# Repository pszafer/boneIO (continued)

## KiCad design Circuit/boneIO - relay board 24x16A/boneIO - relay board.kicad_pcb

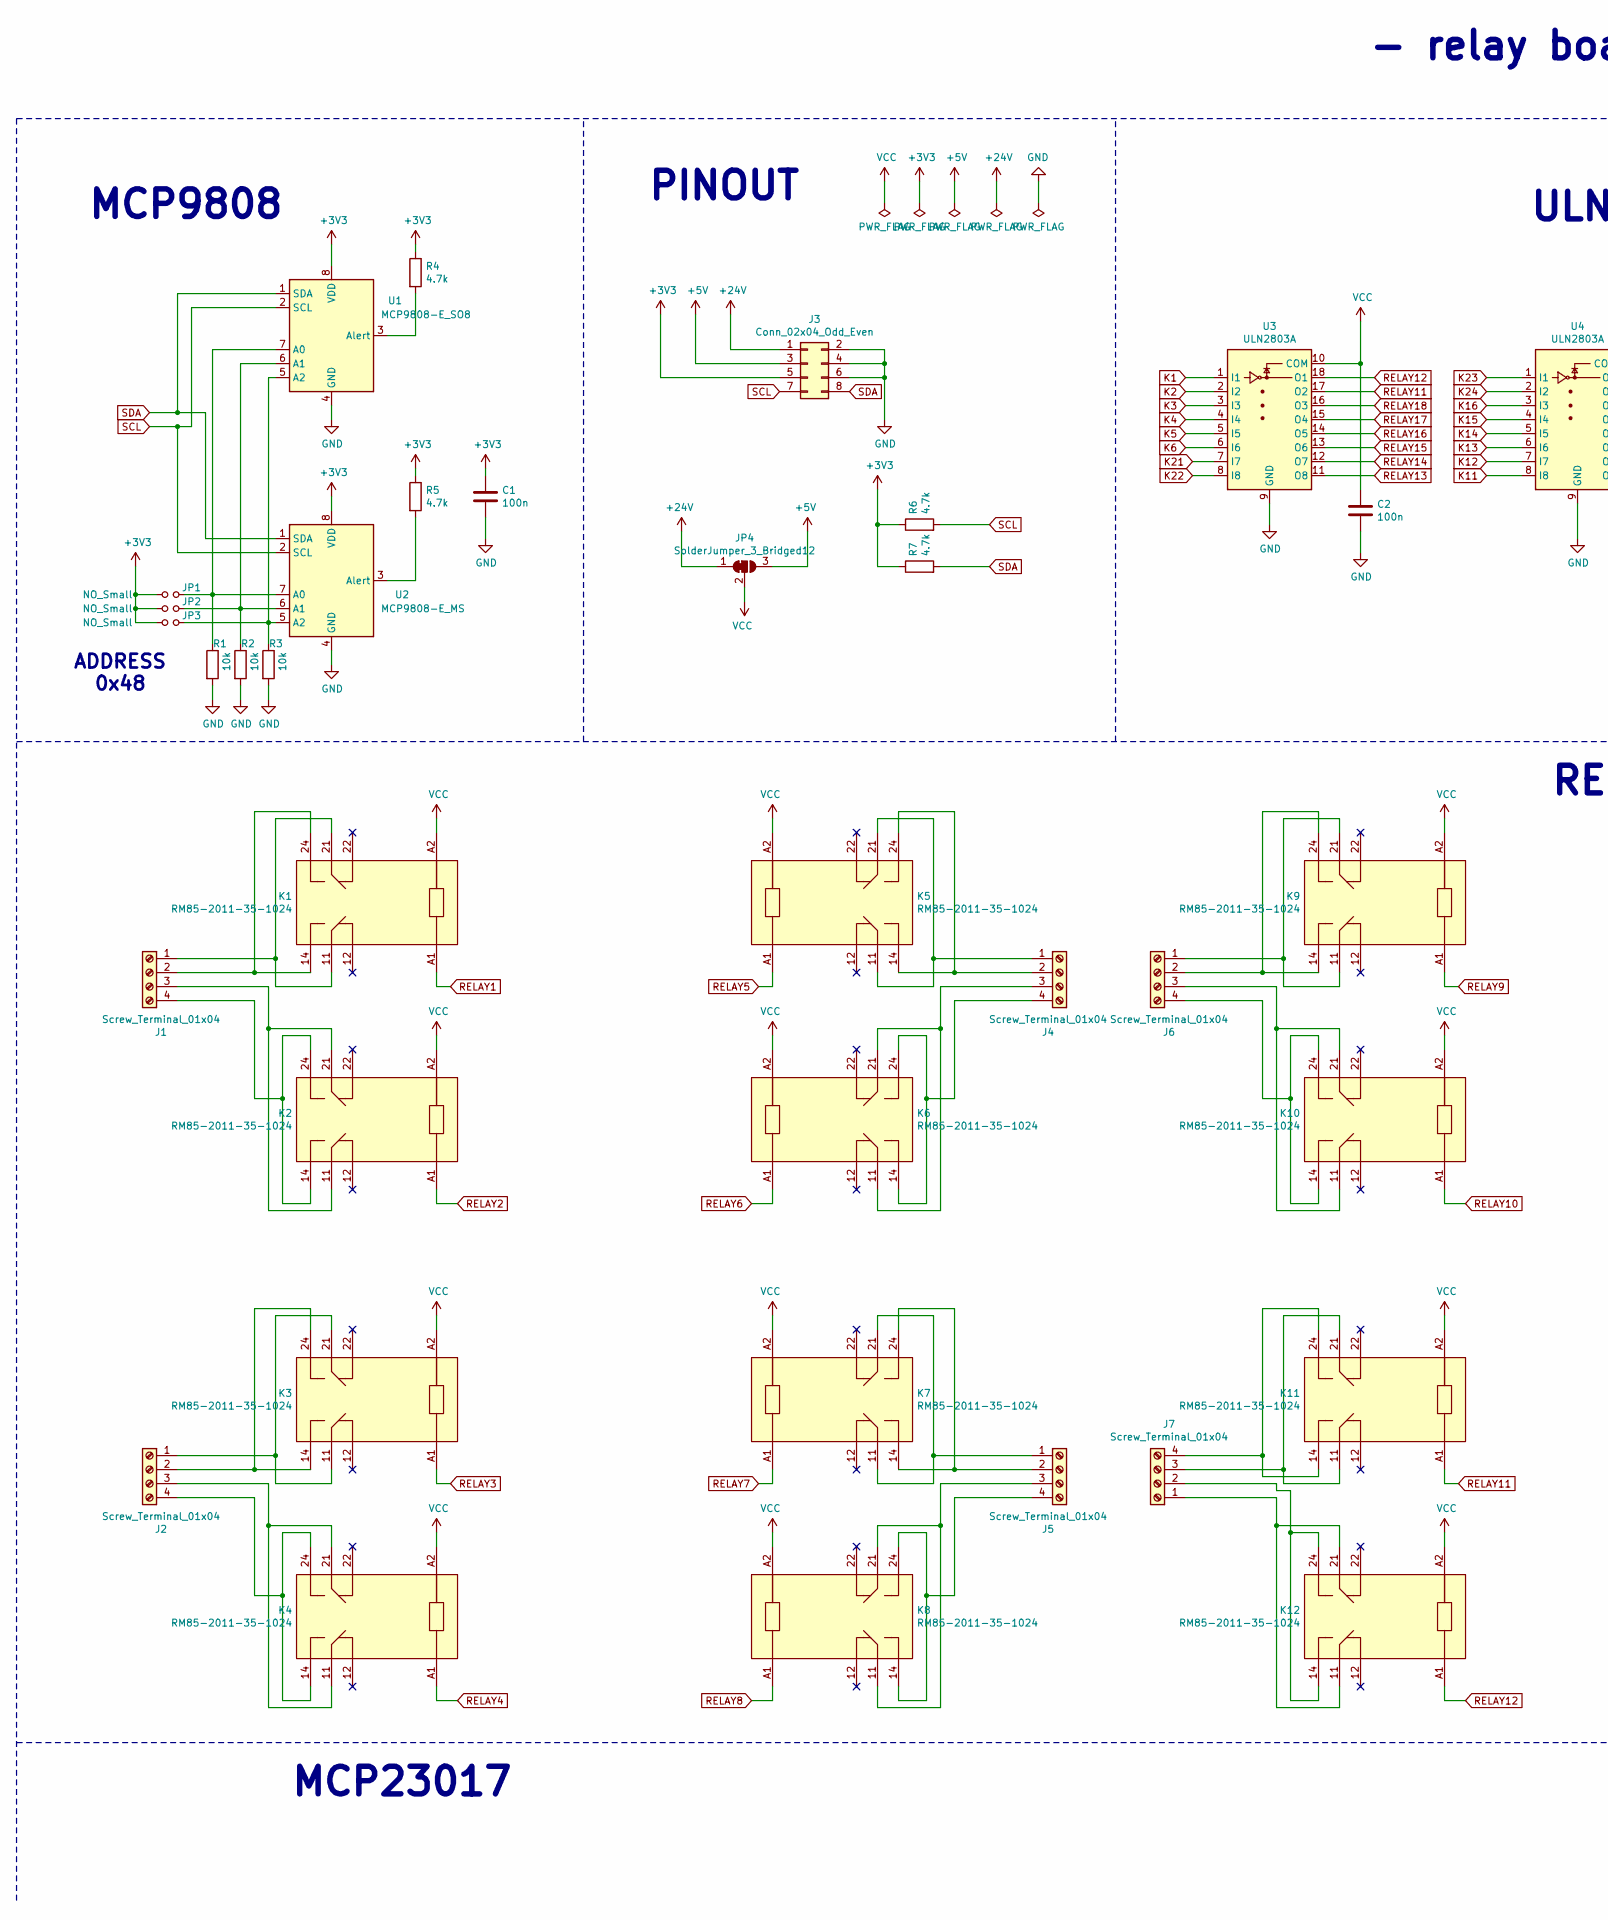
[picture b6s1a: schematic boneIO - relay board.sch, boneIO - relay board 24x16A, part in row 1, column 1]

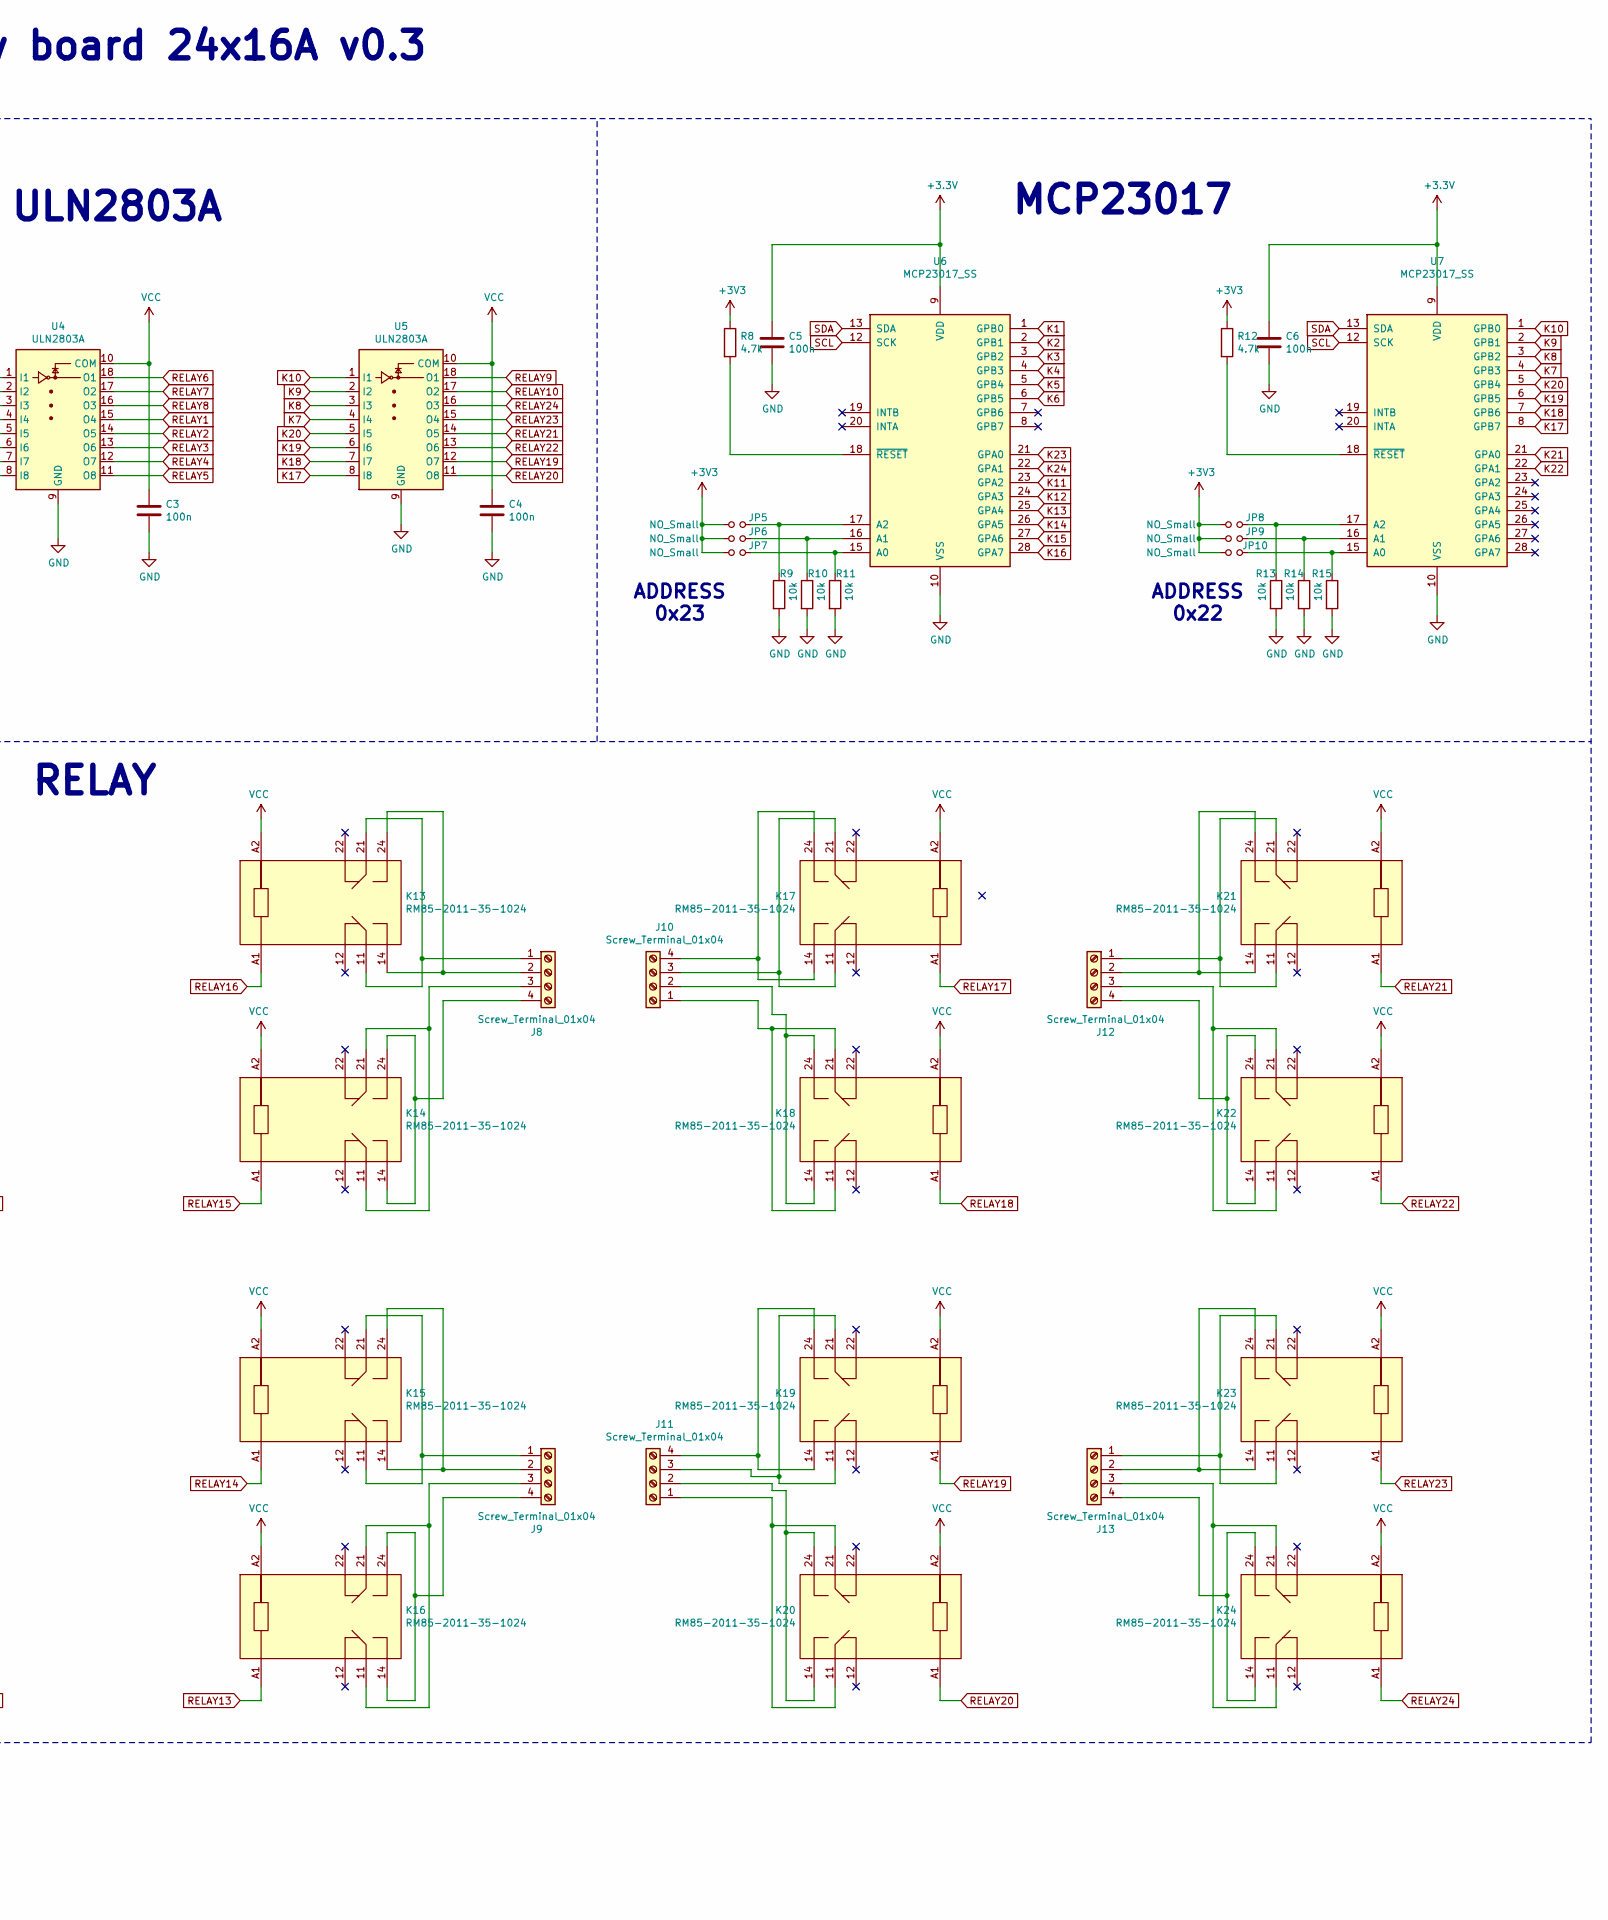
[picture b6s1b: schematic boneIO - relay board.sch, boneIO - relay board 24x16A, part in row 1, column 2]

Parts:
C1, C2, C3, C4, C5, C6: 100n; C_0603_1608Metric
J1, J2, J4, J5, J6, J7, J8, J9, J10, J11, J12, J13: Screw_Terminal_01x04; PhoenixContact_GMSTBA_2,5_4-G_1x04_P7.50mm_Horizontal
J3: Conn_02x04_Odd_Even; PinHeader_2x04_P2.54mm_Vertical
JP1, JP2, JP3, JP5, JP6, JP7, JP8, JP9, JP10: NO_Small; SolderJumper-2_P1.3mm_Open_RoundedPad1.0x1.5mm
JP4: SolderJumper_3_Bridged12; SolderJumper-3_P1.3mm_Bridged12_RoundedPad1.0x1.5mm
K1, K2, K3, K4, K5, K6, K7, K8, K9, K10, K11, K12, K13, K14, K15, K16, K17, K18, K19, K20, K21, K22, K23, K24: RM85-2011-35-1024; RM852011351024
R1, R2, R3, R9, R10, R11, R13, R14, R15: 10k; R_0603_1608Metric
R4, R5, R6, R7, R8, R12: 4.7k; R_0603_1608Metric
U1: MCP9808-E_SO8; SO-8_3.9x4.9mm_P1.27mm
U2: MCP9808-E_MS; SOP65P490X110-8N
U3, U4, U5: ULN2803A; SOIC-18W_7.5x11.6mm_P1.27mm
U6, U7: MCP23017_SS; SSOP-28_5.3x10.2mm_P0.65mm

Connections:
+5V: J3.3, JP4.3 (B)
+24V: J3.1, JP4.1 (A)
GND: C1.2, C2.2, C3.2, C4.2, C5.2, C6.2, J3.2, J3.4, J3.6, R1.2, R2.2, R3.2, R9.2, R10.2, R11.2, R13.2, R14.2, R15.2, U1.4 (GND), U2.4 (GND), U3.9 (GND), U4.9 (GND), U5.9 (GND), U6.10 (VSS), U7.10 (VSS)
K1: U3.1 (I1), U6.1 (GPB0)
K2: U3.2 (I2), U6.2 (GPB1)
K3: U3.3 (I3), U6.3 (GPB2)
K4: U3.4 (I4), U6.4 (GPB3)
K5: U3.5 (I5), U6.5 (GPB4)
K6: U3.6 (I6), U6.6 (GPB5)
K7: U5.4 (I4), U7.4 (GPB3)
K8: U5.3 (I3), U7.3 (GPB2)
K9: U5.2 (I2), U7.2 (GPB1)
K10: U5.1 (I1), U7.1 (GPB0)
K11: U4.8 (I8), U6.23 (GPA2)
K12: U4.7 (I7), U6.24 (GPA3)
K13: U4.6 (I6), U6.25 (GPA4)
K14: U4.5 (I5), U6.26 (GPA5)
K15: U4.4 (I4), U6.27 (GPA6)
K16: U4.3 (I3), U6.28 (GPA7)
K17: U5.8 (I8), U7.8 (GPB7)
K18: U5.7 (I7), U7.7 (GPB6)
K19: U5.6 (I6), U7.6 (GPB5)
K20: U5.5 (I5), U7.5 (GPB4)
K21: U3.7 (I7), U7.21 (GPA0)
K22: U3.8 (I8), U7.22 (GPA1)
K23: U4.1 (I1), U6.21 (GPA0)
K24: U4.2 (I2), U6.22 (GPA1)
unnamed: J1.1, K1.11, K1.21
unnamed: J1.2, K1.14, K1.24
unnamed: J1.3, K2.11, K2.21
unnamed: J1.4, K2.14, K2.24
unnamed: J2.1, K3.11, K3.21
unnamed: J2.2, K3.14, K3.24
unnamed: J2.3, K4.11, K4.21
unnamed: J2.4, K4.14, K4.24
unnamed: J4.1, K5.11, K5.21
unnamed: J4.2, K5.14, K5.24
unnamed: J4.3, K6.11, K6.21
unnamed: J4.4, K6.14, K6.24
unnamed: J5.1, K7.11, K7.21
unnamed: J5.2, K7.14, K7.24
unnamed: J5.3, K8.11, K8.21
unnamed: J5.4, K8.14, K8.24
unnamed: J6.1, K9.11, K9.21
unnamed: J6.2, K9.14, K9.24
unnamed: J6.3, K10.11, K10.21
unnamed: J6.4, K10.14, K10.24
unnamed: J7.1, K12.11, K12.21
unnamed: J7.2, K12.14, K12.24
unnamed: J7.3, K11.11, K11.21
unnamed: J7.4, K11.14, K11.24
unnamed: J8.1, K13.11, K13.21
unnamed: J8.2, K13.14, K13.24
unnamed: J8.3, K14.11, K14.21
unnamed: J8.4, K14.14, K14.24
unnamed: J9.1, K15.11, K15.21
unnamed: J9.2, K15.14, K15.24
unnamed: J9.3, K16.11, K16.21
unnamed: J9.4, K16.14, K16.24
unnamed: J10.1, K18.11, K18.21
unnamed: J10.2, K18.14, K18.24
unnamed: J10.3, K17.11, K17.21
unnamed: J10.4, K17.14, K17.24
unnamed: J11.1, K20.11, K20.21
unnamed: J11.2, K20.14, K20.24
unnamed: J11.3, K19.11, K19.21
unnamed: J11.4, K19.14, K19.24
unnamed: J12.1, K21.11, K21.21
unnamed: J12.2, K21.14, K21.24
unnamed: J12.3, K22.11, K22.21
unnamed: J12.4, K22.14, K22.24
unnamed: J13.1, K23.11, K23.21
unnamed: J13.2, K23.14, K23.24
unnamed: J13.3, K24.11, K24.21
unnamed: J13.4, K24.14, K24.24
unnamed: JP1.2, R1.1, U1.7 (A0), U2.7 (A0)
unnamed: JP2.2, R2.1, U1.6 (A1), U2.6 (A1)
unnamed: JP3.2, R3.1, U1.5 (A2), U2.5 (A2)
unnamed 78: JP5.2, R9.1, U6.17 (A2); also elsewhere on the board
unnamed 79: JP6.2, R10.1, U6.16 (A1); also elsewhere on the board
unnamed 80: JP7.2, R11.1, U6.15 (A0); also elsewhere on the board
unnamed 81: JP8.2, R13.1, U7.17 (A2); also elsewhere on the board
unnamed 82: JP9.2, R14.1, U7.16 (A1); also elsewhere on the board
unnamed 83: JP10.2, R15.1, U7.15 (A0); also elsewhere on the board
unnamed: R4.2, U1.3 (Alert)
unnamed: R5.2, U2.3 (Alert)
unnamed: R8.2, U6.18 (~RESET~)
unnamed: R12.2, U7.18 (~RESET~)
RELAY1: K1.A1, U4.15 (O4)
RELAY2: K2.A1, U4.14 (O5)
RELAY3: K3.A1, U4.13 (O6)
RELAY4: K4.A1, U4.12 (O7)
RELAY5: K5.A1, U4.11 (O8)
RELAY6: K6.A1, U4.18 (O1)
RELAY7: K7.A1, U4.17 (O2)
RELAY8: K8.A1, U4.16 (O3)
RELAY9: K9.A1, U5.18 (O1)
RELAY10: K10.A1, U5.17 (O2)
RELAY11: K11.A1, U3.17 (O2)
RELAY12: K12.A1, U3.18 (O1)
RELAY13: K16.A1, U3.11 (O8)
RELAY14: K15.A1, U3.12 (O7)
RELAY15: K14.A1, U3.13 (O6)
RELAY16: K13.A1, U3.14 (O5)
RELAY17: K17.A1, U3.15 (O4)
RELAY18: K18.A1, U3.16 (O3)
RELAY19: K19.A1, U5.12 (O7)
RELAY20: K20.A1, U5.11 (O8)
RELAY21: K21.A1, U5.14 (O5)
RELAY22: K22.A1, U5.13 (O6)
RELAY23: K23.A1, U5.15 (O4)
RELAY24: K24.A1, U5.16 (O3)
SCL: J3.7, R6.2, U1.2 (SCL), U2.2 (SCL), U6.12 (SCK), U7.12 (SCK)
SDA: J3.8, R7.2, U1.1 (SDA), U2.1 (SDA), U6.13 (SDA), U7.13 (SDA)
VCC: C2.1, C3.1, C4.1, JP4.2 (C), K1.A2, K2.A2, K3.A2, K4.A2, K5.A2, K6.A2, K7.A2, K8.A2, K9.A2, K10.A2, K11.A2, K12.A2, K13.A2, K14.A2, K15.A2, K16.A2, K17.A2, K18.A2, K19.A2, K20.A2, K21.A2, K22.A2, K23.A2, K24.A2, U3.10 (COM), U4.10 (COM), U5.10 (COM)

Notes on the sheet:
PINOUT
ULN2803A
RELAY
MCP9808
MCP23017
- relay board 24x16A v0.3
ADDRESS 0x22
ADDRESS 0x23
ADDRESS 0x48

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
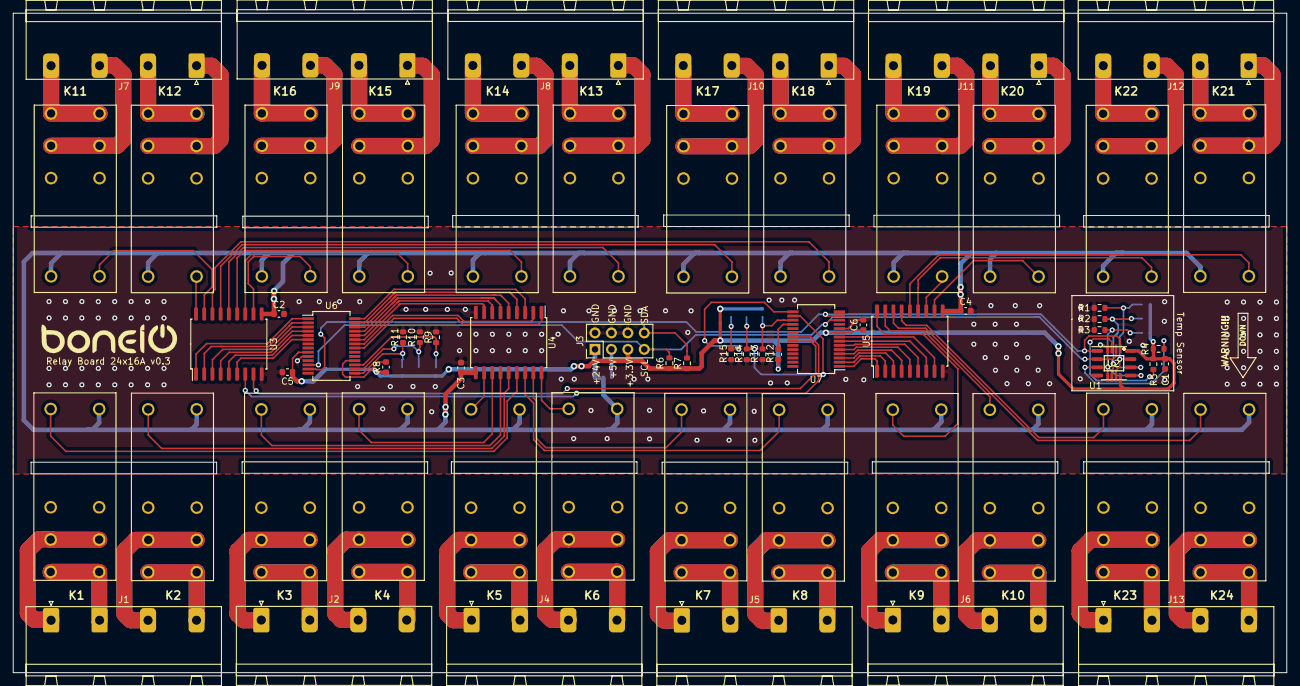
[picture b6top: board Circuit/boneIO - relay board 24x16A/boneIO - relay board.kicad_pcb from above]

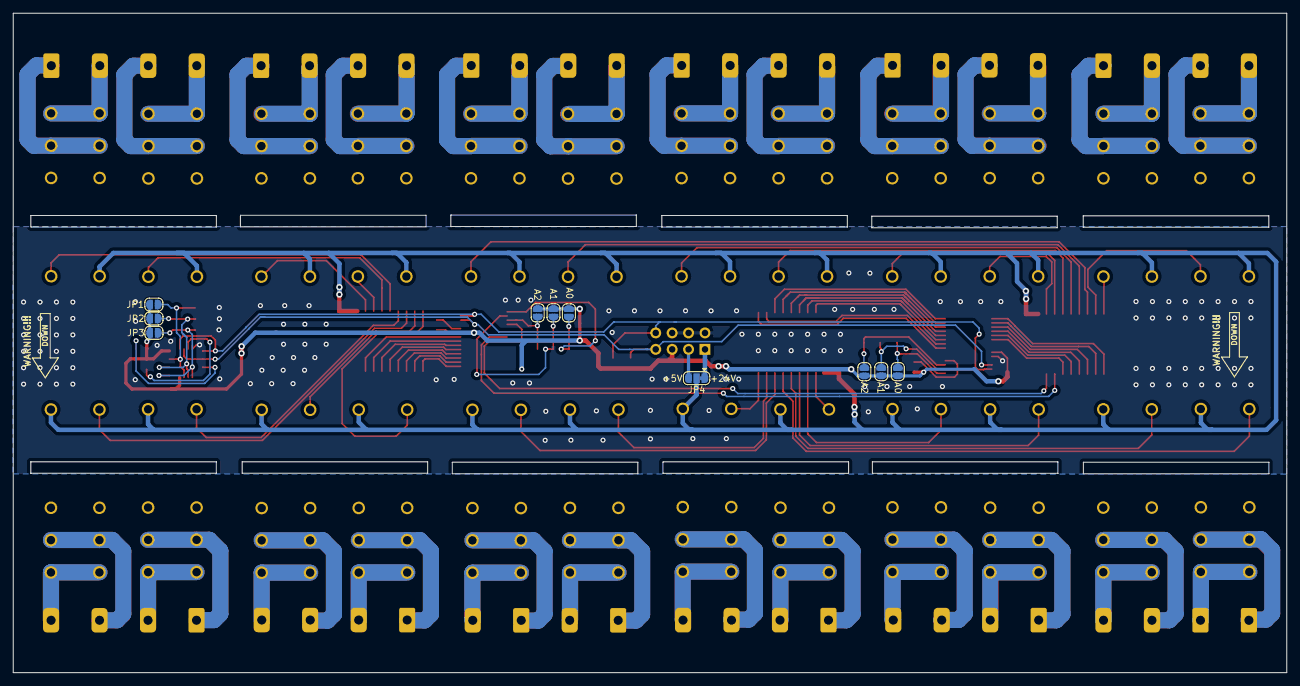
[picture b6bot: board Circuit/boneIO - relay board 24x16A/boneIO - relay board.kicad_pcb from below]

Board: 2 copper layers, 197.0 x 102.0 mm, 75 parts (10 on the bottom side), 116 nets.

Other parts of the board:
A0, A0#2, A1, A1#2, A2, A2#2: NO_Small; SolderJumper-2_P1.3mm_Open_RoundedPad1.0x1.5mm

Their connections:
unnamed 78: A2#2.2; also elsewhere on the board
unnamed 79: A1#2.2; also elsewhere on the board
unnamed 80: A0#2.2; also elsewhere on the board
unnamed 81: A2.2; also elsewhere on the board
unnamed 82: A1.2; also elsewhere on the board
unnamed 83: A0.2; also elsewhere on the board
